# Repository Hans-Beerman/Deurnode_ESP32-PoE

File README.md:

**KiCaD (concept) design Deurnode nieuw**

Current version: concept V0.8

This repository contains the KiCad design for Deurnode nieuw, a deurnode for the Makerspace Leiden. This new design is based on the use of an Olimex ESP32-PoE.

**This Deurnode Nieuw has the following features:**

- Two digital inputs van be used. The following options are available:
	Option 1:
 	- 1x Simple digital switch input (to be used for the Grote Schakelaar e.g.).
 	- 1x Opto coupler input.
	Remark:
	If input Schakelaar is not used, C1 could be removed

	Option 2:
  - 2x opto coupler input.

	Both opto couplers can detect 230V AC available or not. By changing the input resistors of the optocouplers the inputs can be used for other voltages as well.

- 1 digital output is available. The following options are available:
  - Digital output, to directly control a buzzer.
  - Digital output to switch a coil or so. There are two options:
    - A relais controlled isolated output (max. 250V AC/10A).
    - A FET based output using the 12V power from an external power supply.
	The FET can handle max DC 55V/30 A. In our case max Ids is much less, due to to low maximum gateway voltage of about 3V. In case it is needed, the FET can be kept cool by means of a small cool block.
	For testing purposes, both the relais and the FET can be switched on permanently by placing jumper "Rel./FET Override".

- SPI based RFID reader connection..

- Step motor output, based on Polu Breakout A4988.

**Power supply:**

Depending on how the deurnode is used, there are two options to provide power to the deurnode print:

1. The ethernet port of the Olimex ESP32-PoE board is directly connected to the MSL LAN. Jumper J19 (Use external 12V) must be removed in this situation. In that case there is no 12V available. It is however possible to provide 12V with an external PSU. Without external 12 V the step motor and the buzzer will not function at all and also the 12V output for the FET will not be available.
2. To power the board via an external PSU (only). J19 must be installed and the ethernet board of the Olimex board should not be connected to a PoE switch port.

The following solution is available to couple the deurnode directly to a PoE connection of MSL LAN and also provide 12V to the deurnode board. See the diagram in the file &quot;Deurnode Nieuw power supply V0.1 20200302.pdf&quot;

For this solution a PoE splitter is used. On the Deurnode board jumper J19 must be installed.

**Protection 230V circuits for the opto couplers**

To prevent hazardous shocks, a plexiglass plate can be mounted on the board. The board contains 3 holes to mount a plate.

For more information about these protection plates, see the &quot;DeurnodeProtection-230V V0.2 20200308.pdf&quot; or the Autocad &quot;DeurnodeProtection-230V.dwg&quot; files.

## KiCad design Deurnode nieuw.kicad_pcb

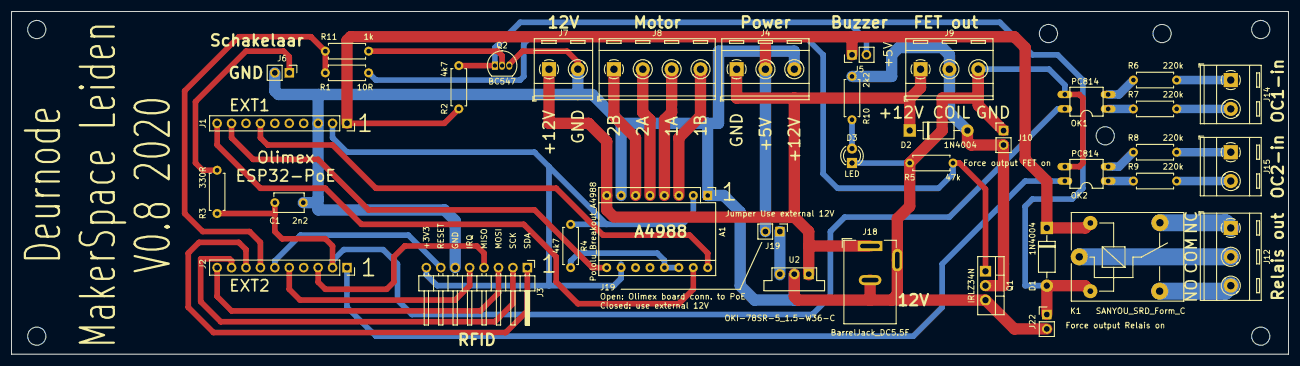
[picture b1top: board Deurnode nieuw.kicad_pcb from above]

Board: 2 copper layers, 224.8 x 60.3 mm, 38 parts (0 on the bottom side), 39 nets.

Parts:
A1: Pololu_Breakout_A4988; Pololu_Breakout-16_15.2x20.3mm
C1: 2n2; C_Disc_D5.1mm_W3.2mm_P5.00mm
D1, D2: 1N4004; D_DO-41_SOD81_P10.16mm_Horizontal
D3: LED; LED_D3.0mm
J1: EXT1; PinSocket_1x10_P2.54mm_Vertical
J2: EXT2; PinSocket_1x10_P2.54mm_Vertical
J3: Conn_01x08; PinHeader_1x08_P2.54mm_Horizontal
J4, J9, J12: Screw_Terminal_01x03; TerminalBlock_RND_205-00288_1x03_P5.08mm_Horizontal
J5, J6: Conn_01x02; PinHeader_1x02_P2.54mm_Vertical
J7, J14, J15: Screw_Terminal_01x02; TerminalBlock_RND_205-00287_1x02_P5.08mm_Horizontal
J8: Screw_Terminal_01x04; TerminalBlock_RND_205-00289_1x04_P5.08mm_Horizontal
J10: Force output FET on; PinHeader_1x02_P2.54mm_Vertical
J18: BarrelJack_DC5.5F
J19: Jumper Use external 12V; PinHeader_1x02_P2.54mm_Vertical
J22: Force output Relais on; PinHeader_1x02_P2.54mm_Vertical
K1: SANYOU_SRD_Form_C; Relay_SPDT_SANYOU_SRD_Series_Form_C
OK1, OK2: PC814; DIL04
Q1: IRLZ34N; TO-220-3_Vertical
Q2: BC547; TO-92_Inline
R1: 10R; R_Axial_DIN0207_L6.3mm_D2.5mm_P7.62mm_Horizontal
R2, R4: 4k7; R_Axial_DIN0207_L6.3mm_D2.5mm_P7.62mm_Horizontal
R3: 330R; R_Axial_DIN0207_L6.3mm_D2.5mm_P7.62mm_Horizontal
R5: 47k; R_Axial_DIN0207_L6.3mm_D2.5mm_P7.62mm_Horizontal
R6, R7, R8, R9: 220k; R_Axial_DIN0207_L6.3mm_D2.5mm_P7.62mm_Horizontal
R10: 2k2; R_Axial_DIN0207_L6.3mm_D2.5mm_P7.62mm_Horizontal
R11: 1k; R_Axial_DIN0207_L6.3mm_D2.5mm_P7.62mm_Horizontal
U2: OKI-78SR-5_1.5-W36-C; Converter_DCDC_muRata_OKI-78SR_Vertical

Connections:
3V3: A1.2, A1.10, J1.2, J3.8, R4.1
+5V: D1.1, J1.1, J4.2, J5.1, J19.2, K1.5, R2.1
+12V: A1.8, D2.1, J4.1, J7.1, J9.1, J18.1, U2.1
GND: A1.1, A1.7, C1.2, D3.1, J1.3, J3.6, J4.3, J6.2, J7.2, J9.3, J10.1, J18.2, J18.3, J22.2, OK1.3, OK2.3, Q1.3, Q2.3, R5.2, U2.2
GPI35: J2.3, J3.4
GPI36_U1RXD: C1.1, J2.2, OK1.4, R3.2
GPI39: J2.1, OK2.4
GPIO2_HS2_DATA0: A1.16, J1.7
GPIO4_U1TXD: A1.9, J1.9
GPIO5_SPI_C5: A1.15, J1.10
GPIO13_I2C-SDA: J2.10, J3.3
GPIO14_HS2_CLK: J2.9, J3.2
GPIO15_HS2_CMD: J2.8, J3.1
GPIO16_I2C-SCL: J2.7, R1.2, R11.2
GPIO32: J2.6, J3.7
GPIO33: J2.5, J3.5
unnamed: A1.3, J8.4
unnamed: A1.4, J8.3
unnamed: A1.5, J8.2
unnamed: A1.6, J8.1
unnamed: A1.13, A1.14, R4.2
unnamed: D1.2, J5.2, J22.1, K1.2, Q2.1, R2.2
unnamed: D2.2, J9.2, J10.2, Q1.2, R10.1
unnamed: D3.2, R10.2
unnamed: J6.1, R3.1
unnamed: J12.1, K1.4
unnamed: J12.2, K1.1
unnamed: J12.3, K1.3
unnamed: J14.1, R6.1
unnamed: J14.2, R7.1
unnamed: J15.1, R8.1
unnamed: J15.2, R9.1
unnamed: J19.1, U2.3
unnamed: OK1.1, R7.2
unnamed: OK1.2, R6.2
unnamed: OK2.1, R9.2
unnamed: OK2.2, R8.2
unnamed: Q1.1, R1.1, R5.1
unnamed: Q2.2, R11.1

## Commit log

2020-02-27 First publisched concept version
2020-02-28 Second publisched concept version
2020-02-28 Second publisched concept version + schematics pdf
2020-03-02 DC-DC converter 12V -> 5V added to concept version 0.3
2020-03-02 README.md and other docs added, additional 12V connector added to design concept version 0.4
2020-03-02 README.md changed, still on concept version 0.4
2020-03-02 Replaced old version of Deurnode nieuw.pdf, still on concept version 0.4
2020-03-02 Create LICENSE
2020-03-03 By means of two jumpers the FET components are isolated from the rest of the board. Current concept version 0.5
2020-03-05 Jumper added for Relais/FET override + correct footprint made for 12V barel jack current version concept V0.6
2020-03-06 Readme.md pdated to reflect changes in current concept version 0.6
2020-03-08 removed a lot of jumpers, replaced connectors, added groundplane etc.
2020-03-08 Relais and FET are controlled separately, buzzer resistor added. Current version Concep V0.8
